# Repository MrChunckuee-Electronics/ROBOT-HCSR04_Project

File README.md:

# Robot_HC-SR04
***
Para mas archivos de los proyectos de robótica te invito a visitar [MrChuckuee Electronics](http://mrchunckuee.blogspot.mx/p/robotica.html) 

***
Puedes seguirme en:
- [Blogspot](http://mrchunckuee.blogspot.com)
- [Instagram](https://www.instagram.com/mrchunckuee_electronics/)
- [Facebook](https://www.facebook.com/MrChunckueeElectronics)
- [Twitter](https://twitter.com/MrChunckuee)
- [YouTube](https://www.youtube.com/@MrChunckueeElectronics)

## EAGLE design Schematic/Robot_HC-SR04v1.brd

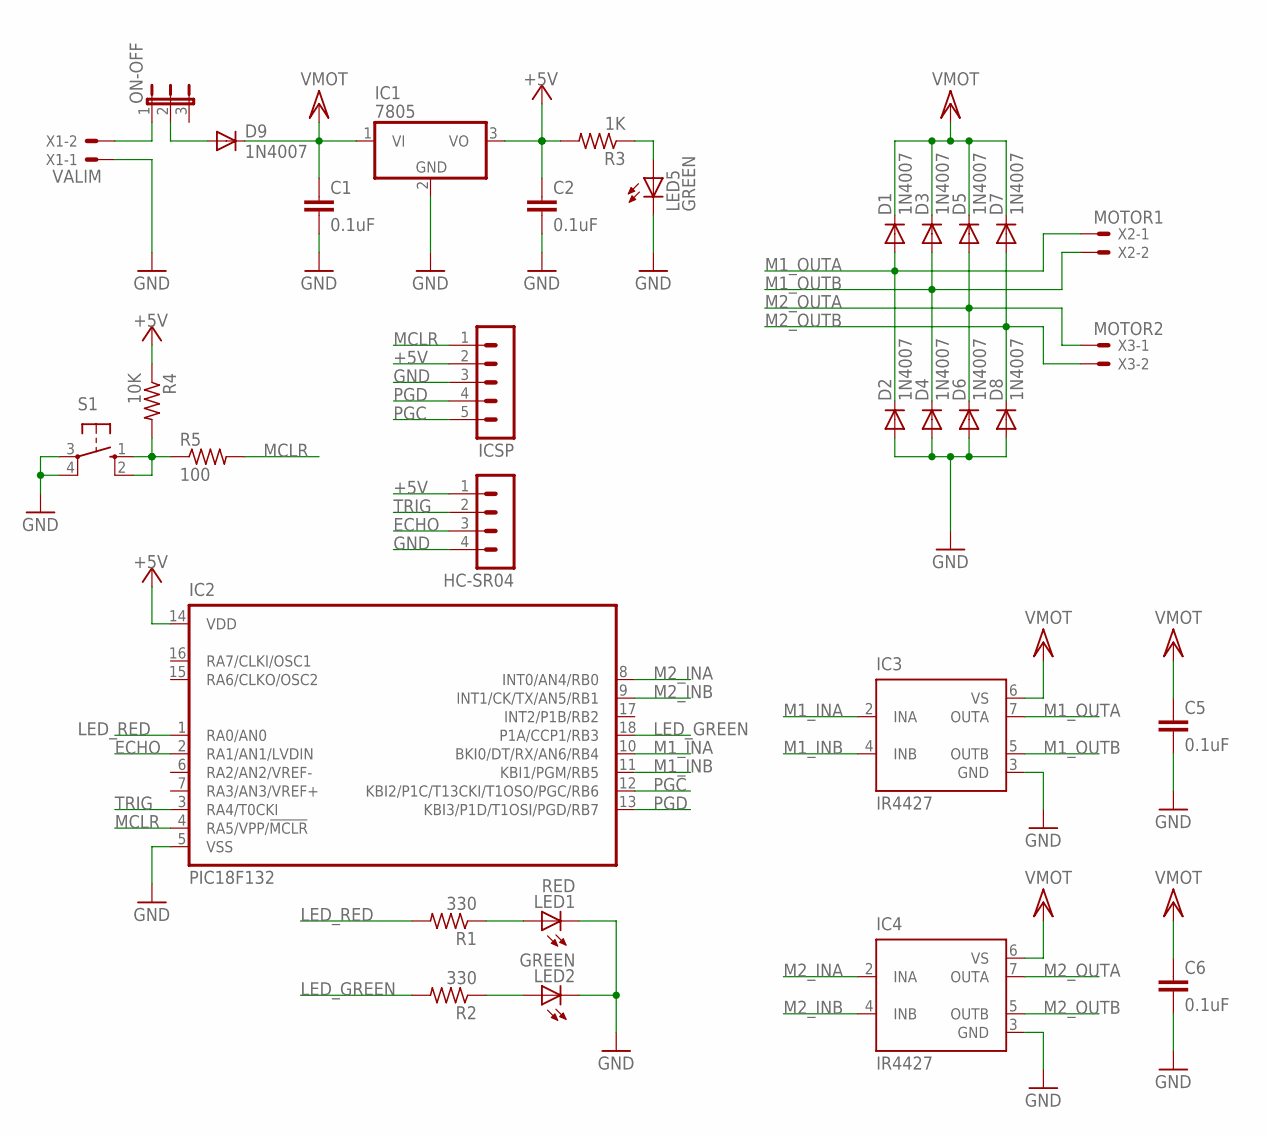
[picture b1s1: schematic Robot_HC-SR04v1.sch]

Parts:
C1, C2, C5, C6: 0.1uF; C050-024X044
D1, D2, D3, D4, D5, D6, D7, D8, D9: 1N4007; DO41-10
HC-SR04: MA04-1
IC1: 7805; TO220H
IC2: PIC18F132; SO-18W
IC3, IC4: IR4427; DIL08
ICSP: MA05-1
LED1: RED; LED3MM
LED2, LED5: GREEN; LED3MM
ON-OFF: JP2E; JP2
R1, R2: 330; 0207/7
R3: 1K; 0207/7
R4: 10K; 0207/7
R5: 100; 0207/7
S1: 10-XX; B3F-10XX
X1: VALIM; 22-23-2021
X2: MOTOR1; 22-23-2021
X3: MOTOR2; 22-23-2021

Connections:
+5V: C2.1, HC-SR04.1, IC1.3 (VO), IC2.14 (VDD), ICSP.2, R3.2, R4.1
ECHO: HC-SR04.3, IC2.2 (RA1/AN1/LVDIN)
GND: C1.2, C2.2, C5.2, C6.2, D2.A, D4.A, D6.A, D8.A, HC-SR04.4, IC1.2 (GND), IC2.5 (VSS), IC3.3 (GND), IC4.3 (GND), ICSP.3, LED1.K (C), LED2.K (C), LED5.K (C), S1.3, S1.4 (P1), X1.1
LED_GREEN: IC2.18 (P1A/CCP1/RB3), R2.2
LED_RED: IC2.1 (RA0/AN0), R1.2
M1_INA: IC2.10 (BKI0/DT/RX/AN6/RB4), IC3.2 (INA)
M1_INB: IC2.11 (KBI1/PGM/RB5), IC3.4 (INB)
M1_OUTA: D1.A, D2.C, IC3.7 (OUTA), X2.1
M1_OUTB: D3.A, D4.C, IC3.5 (OUTB), X2.2
M2_INA: IC2.8 (INT0/AN4/RB0), IC4.2 (INA)
M2_INB: IC2.9 (INT1/CK/TX/AN5/RB1), IC4.4 (INB)
M2_OUTA: D5.A, D6.C, IC4.7 (OUTA), X3.1
M2_OUTB: D7.A, D8.C, IC4.5 (OUTB), X3.2
MCLR: IC2.4 (RA5/VPP/!MCLR), ICSP.1, R5.2
unnamed: LED5.A, R3.1
unnamed: R4.2, R5.1, S1.1 (S), S1.2 (S1)
unnamed: D9.A, ON-OFF.2
unnamed: ON-OFF.1, X1.2
unnamed: LED1.A, R1.1
unnamed: LED2.A, R2.1
PGC: IC2.12 (KBI2/P1C/T13CKI/T1OSO/PGC/RB6), ICSP.5
PGD: IC2.13 (KBI3/P1D/T1OSI/PGD/RB7), ICSP.4
TRIG: HC-SR04.2, IC2.3 (RA4/T0CKI)
VCC/2: C1.1, C5.1, C6.1, D1.C, D3.C, D5.C, D7.C, D9.C, IC1.1 (VI), IC3.6 (VS), IC4.6 (VS)

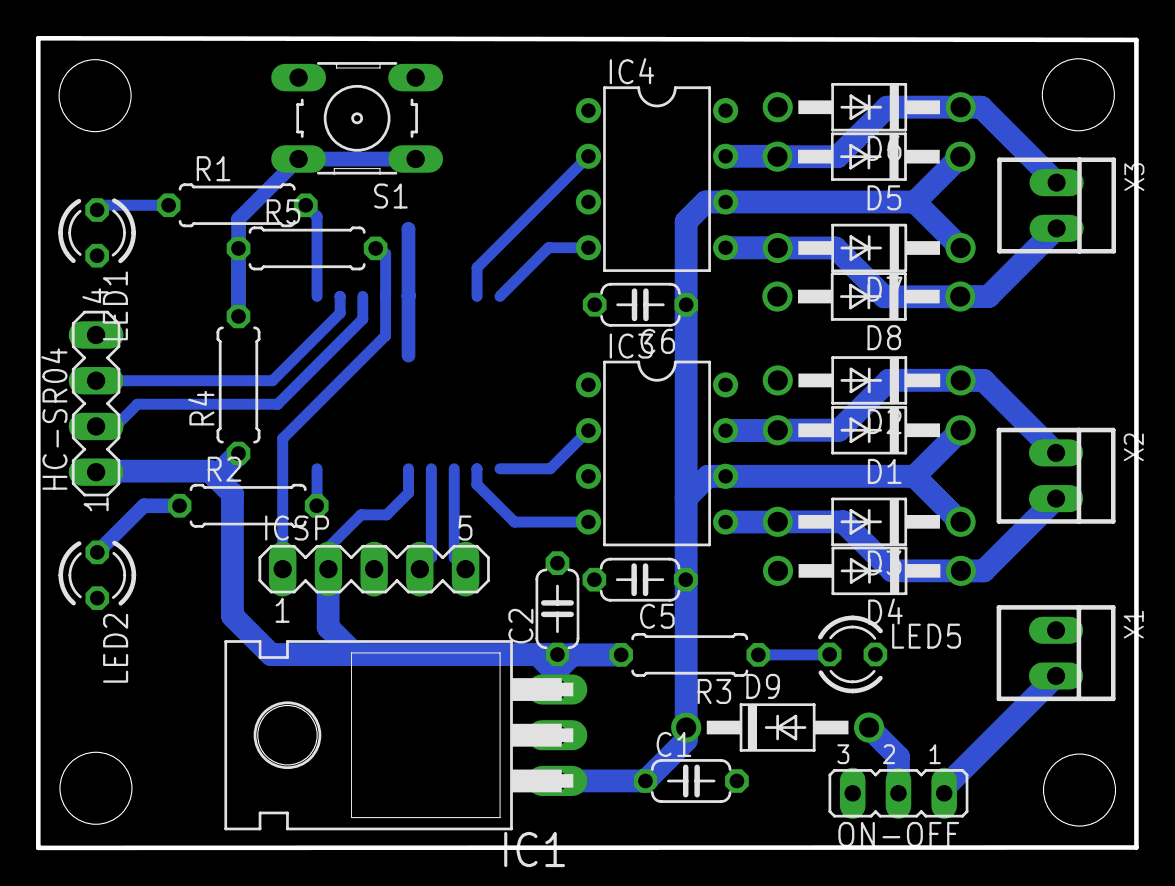
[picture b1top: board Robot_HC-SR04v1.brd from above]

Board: 2 copper layers, 61.0 x 45.0 mm, 32 parts (1 on the bottom side), 24 nets.

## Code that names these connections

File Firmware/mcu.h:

/* 
 * File:   mcu.h
 * Author: MrChunckuee
 *
 * Created on 20 de mayo de 2013, 09:48 PM
 */

#ifndef MCU_H
#define	MCU_H

#define HIGH    1
#define LOW     0
#define INPUT   1
#define OUTPUT  0
#define CLEAR   0x00

#define MOTOR_IZQUIERDA_INA          PORTBbits.RB0
#define TRIS_MOTOR_IZQUIERDA_INA     TRISB0
#define MOTOR_IZQUIERDA_INB          PORTBbits.RB1
#define TRIS_MOTOR_IZQUIERDA_INB     TRISB1

#define MOTOR_DERECHA_INA            PORTBbits.RB4
#define TRIS_MOTOR_DERECHA_INA       TRISB4
#define MOTOR_DERECHA_INB            PORTBbits.RB5
#define TRIS_MOTOR_DERECHA_INB       TRISB5

#define LED_DERECHA                  PORTAbits.RA0
#define TRIS_LED_DERECHA             TRISA0
#define LED_IZQUIERDA                PORTBbits.RB3
#define TRIS_LED_IZQUIERDA           TRISB3

#define TRIG                         PORTAbits.RA4
#define TRIS_TRIG                    TRISA4
#define ECHO                         PORTAbits.RA1
#define TRIS_ECHO                    TRISA1

void MCU_Init(void);
void Delay_MS(unsigned int t);
unsigned int Medir_Distancia(void);
void Navegacion(void);
void Opcion_Movimiento(unsigned char X);

#endif	/* MCU_H */

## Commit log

2017-09-22 Robot_HC-SR04 v1.0
2017-09-22 Robot_HC-SR04
